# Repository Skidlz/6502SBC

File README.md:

6502SBC
=======

6502 Single Board Computer

Schematics done in eagle 6.1

Source assembles with CA65

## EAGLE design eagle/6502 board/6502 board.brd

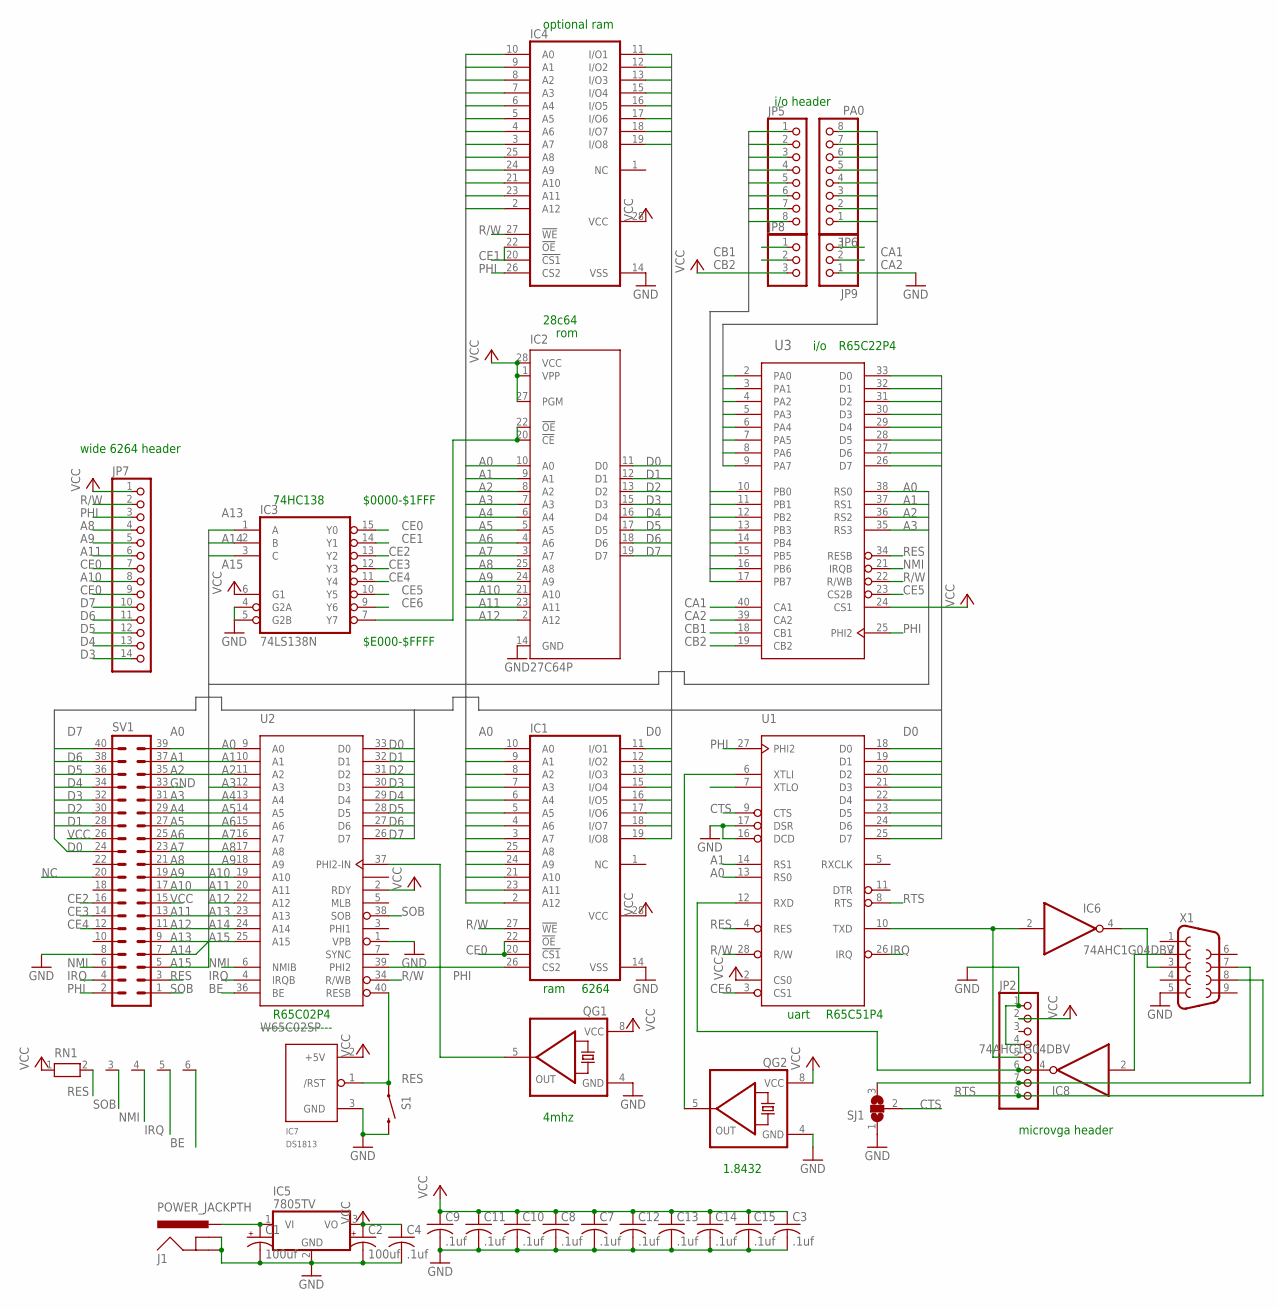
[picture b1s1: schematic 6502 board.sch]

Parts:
C1: 100uf; E3,5-8
C2: 100uf; E2,5-6
C3, C4, C7, C8, C9, C10, C11, C12, C13, C14, C15: .1uf; C025-024X044
IC1, IC4: 6264ASMALL; DIL28-3
IC2: 27C64P; DIL28-6
IC3: 74LS138N; DIL16
IC5: 7805TV; TO220V
IC6, IC8: 74AHC1G04DBV; SOT23-5
IC7: DS1813; TO-92
J1: POWER_JACKPTH; POWER_JACK_PTH
JP2, JP5, JP6: PINHD-1X8BIG; 1X08-BIG
JP7: PINHD-1X14-CB; 1X14-CB
JP8, JP9: PINHD-1X3; 1X03
QG1, QG2: QG5460; DIL08S
RN1: RN05; RN-6
S1: SWITCH-MOMENTARY-2PTH; TACTILE-PTH
SJ1: SJ2WW; SJ_2W
SV1: ML40
U1: G65SC51P; DIP-28
U2: W65C02SP; DIP-40
U3: G65SC22P; DIP-40
X1: DB9FEMALE; DB9

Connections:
A0: IC1.10 (A0), IC2.10 (A0), IC4.10 (A0), SV1.39, U1.13 (RS0), U2.9 (A0), U3.38 (RS0)
A1: IC1.9 (A1), IC2.9 (A1), IC4.9 (A1), SV1.37, U1.14 (RS1), U2.10 (A1), U3.37 (RS1)
A2: IC1.8 (A2), IC2.8 (A2), IC4.8 (A2), SV1.35, U2.11 (A2), U3.36 (RS2)
A3: IC1.7 (A3), IC2.7 (A3), IC4.7 (A3), SV1.31, U2.12 (A3), U3.35 (RS3)
A4: IC1.6 (A4), IC2.6 (A4), IC4.6 (A4), SV1.29, U2.13 (A4)
A5: IC1.5 (A5), IC2.5 (A5), IC4.5 (A5), SV1.27, U2.14 (A5)
A6: IC1.4 (A6), IC2.4 (A6), IC4.4 (A6), SV1.25, U2.15 (A6)
A7: IC1.3 (A7), IC2.3 (A7), IC4.3 (A7), SV1.23, U2.16 (A7)
A8: IC1.25 (A8), IC2.25 (A8), IC4.25 (A8), JP7.4, SV1.21, U2.17 (A8)
A9: IC1.24 (A9), IC2.24 (A9), IC4.24 (A9), JP7.5, SV1.19, U2.18 (A9)
A10: IC1.21 (A10), IC2.21 (A10), IC4.21 (A10), JP7.8, SV1.17, U2.19 (A10)
A11: IC1.23 (A11), IC2.23 (A11), IC4.23 (A11), JP7.6, SV1.13, U2.20 (A11)
A12: IC1.2 (A12), IC2.2 (A12), IC4.2 (A12), SV1.11, U2.22 (A12)
A13: IC3.1 (A), SV1.9, U2.23 (A13)
A14: IC3.2 (B), SV1.7, U2.24 (A14)
A15: IC3.3 (C), SV1.5, U2.25 (A15)
BE: RN1.6, U2.36 (BE)
CA1: JP9.3, U3.40 (CA1)
CA2: JP9.2, U3.39 (CA2)
CB1: JP8.1, U3.18 (CB1)
CB2: JP8.2, U3.19 (CB2)
CE0: IC1.20 (!CS1), IC1.22 (!OE), IC3.15 (Y0), JP7.7, JP7.9
CE1: IC3.14 (Y1), IC4.20 (!CS1), IC4.22 (!OE)
CE2: IC3.13 (Y2), SV1.16
CE3: IC3.12 (Y3), SV1.14
CE4: IC3.11 (Y4), SV1.12
CE5: IC3.10 (Y5), U3.23 (CS2B)
CE6: IC3.9 (Y6), U1.3 (CS1)
CTS: SJ1.2, U1.9 (CTS)
D0: IC1.11 (I/O1), IC2.11 (D0), IC4.11 (I/O1), SV1.24, U1.18 (D0), U2.33 (D0), U3.33 (D0)
D1: IC1.12 (I/O2), IC2.12 (D1), IC4.12 (I/O2), SV1.28, U1.19 (D1), U2.32 (D1), U3.32 (D1)
D2: IC1.13 (I/O3), IC2.13 (D2), IC4.13 (I/O3), SV1.30, U1.20 (D2), U2.31 (D2), U3.31 (D2)
D3: IC1.15 (I/O4), IC2.15 (D3), IC4.15 (I/O4), JP7.14, SV1.32, U1.21 (D3), U2.30 (D3), U3.30 (D3)
D4: IC1.16 (I/O5), IC2.16 (D4), IC4.16 (I/O5), JP7.13, SV1.34, U1.22 (D4), U2.29 (D4), U3.29 (D4)
D5: IC1.17 (I/O6), IC2.17 (D5), IC4.17 (I/O6), JP7.12, SV1.36, U1.23 (D5), U2.28 (D5), U3.28 (D5)
D6: IC1.18 (I/O7), IC2.18 (D6), IC4.18 (I/O7), JP7.11, SV1.38, U1.24 (D6), U2.27 (D6), U3.27 (D6)
D7: IC1.19 (I/O8), IC2.19 (D7), IC4.19 (I/O8), JP7.10, SV1.40, U1.25 (D7), U2.26 (D7), U3.26 (D7)
GND: C1.-, C2.-, C3.2, C4.2, C7.2, C8.2, C9.2, C10.2, C11.2, C12.2, C13.2, C14.2, C15.2, IC1.14 (VSS), IC2.14 (GND), IC3.4 (G2A), IC3.5 (G2B), IC3.8 (GND), IC4.14 (VSS), IC5.2 (GND), IC6.3 (GND), IC7.3 (GND), IC8.3 (GND), J1.GND, J1.GNDBREAK, JP2.1, JP2.4, JP9.1, QG1.4 (GND), QG2.4 (GND), S1.3 (2), SJ1.1, SV1.8, SV1.33, U1.16 (DCD), U1.17 (DSR), U2.1 (VPB), X1.5
IRQ: RN1.5, SV1.4, U1.26 (IRQ), U2.4 (IRQB)
unnamed: QG1.5 (OUT), U2.37 (PHI2-IN)
unnamed: IC2.20 (!CE), IC2.22 (!OE), IC3.7 (Y7)
unnamed: IC6.4 (O), X1.3
unnamed: IC8.2 (I), X1.2
unnamed: JP2.7, SJ1.3, X1.7
unnamed: QG2.5 (OUT), U1.6 (XTLI)
unnamed: IC6.2 (I), JP2.5, U1.10 (TXD)
unnamed: IC8.4 (O), JP2.6, U1.12 (RXD)
unnamed: C1.+, IC5.1 (VI), J1.PWR
NC: SV1.20
NMI: RN1.4, SV1.6, U2.6 (NMIB), U3.21 (IRQB)
PA0: JP6.8, U3.2 (PA0)
PA1: JP6.7, U3.3 (PA1)
PA2: JP6.6, U3.4 (PA2)
PA3: JP6.5, U3.5 (PA3)
PA4: JP6.4, U3.6 (PA4)
PA5: JP6.3, U3.7 (PA5)
PA6: JP6.2, U3.8 (PA6)
PA7: JP6.1, U3.9 (PA7)
PB0: JP5.1, U3.10 (PB0)
PB1: JP5.2, U3.11 (PB1)
PB2: JP5.3, U3.12 (PB2)
PB3: JP5.4, U3.13 (PB3)
PB4: JP5.5, U3.14 (PB4)
PB5: JP5.6, U3.15 (PB5)
PB6: JP5.7, U3.16 (PB6)
PB7: JP5.8, U3.17 (PB7)
PHI: IC1.26 (CS2), IC4.26 (CS2), JP7.3, SV1.2, U1.27 (PHI2), U2.39 (PHI2), U3.25 (PHI2)
R/W: IC1.27 (!WE), IC4.27 (!WE), JP7.2, U1.28 (R/W), U2.34 (R/WB), U3.22 (R/WB)
RES: IC7.1 (/RST), RN1.2, S1.1, SV1.3, U1.4 (RES), U2.40 (RESB), U3.34 (RESB)
RTS: JP2.8, U1.8 (RTS), X1.8
SOB: RN1.3, SV1.1, U2.38 (SOB)
VCC: C2.+, C3.1, C4.1, C7.1, C8.1, C9.1, C10.1, C11.1, C12.1, C13.1, C14.1, C15.1, IC1.28 (VCC), IC2.1 (VPP), IC2.27 (PGM), IC2.28 (VCC), IC3.6 (G1), IC3.16 (VCC), IC4.28 (VCC), IC5.3 (VO), IC6.5 (VCC), IC7.2 (+5V), IC8.5 (VCC), JP2.2, JP7.1, JP8.3, QG1.8 (VCC), QG2.8 (VCC), RN1.1, SV1.15, SV1.26, U1.2 (CS0), U2.2 (RDY), U3.24 (CS1)
VDD: U1.15 (VDD), U2.8 (VDD), U3.20 (VDD)
VSS: U1.1 (VSS), U2.21 (VSS), U3.1 (VSS)

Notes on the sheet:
microvga header
rom
ram
4mhz
1.8432
$0000-$1FFF
$E000-$FFFF
uart
i/o
R65C22P4
R65C51P4
R65C02P4
------------------
6264
i/o header
28c64
74HC138
optional ram
wide 6264 header

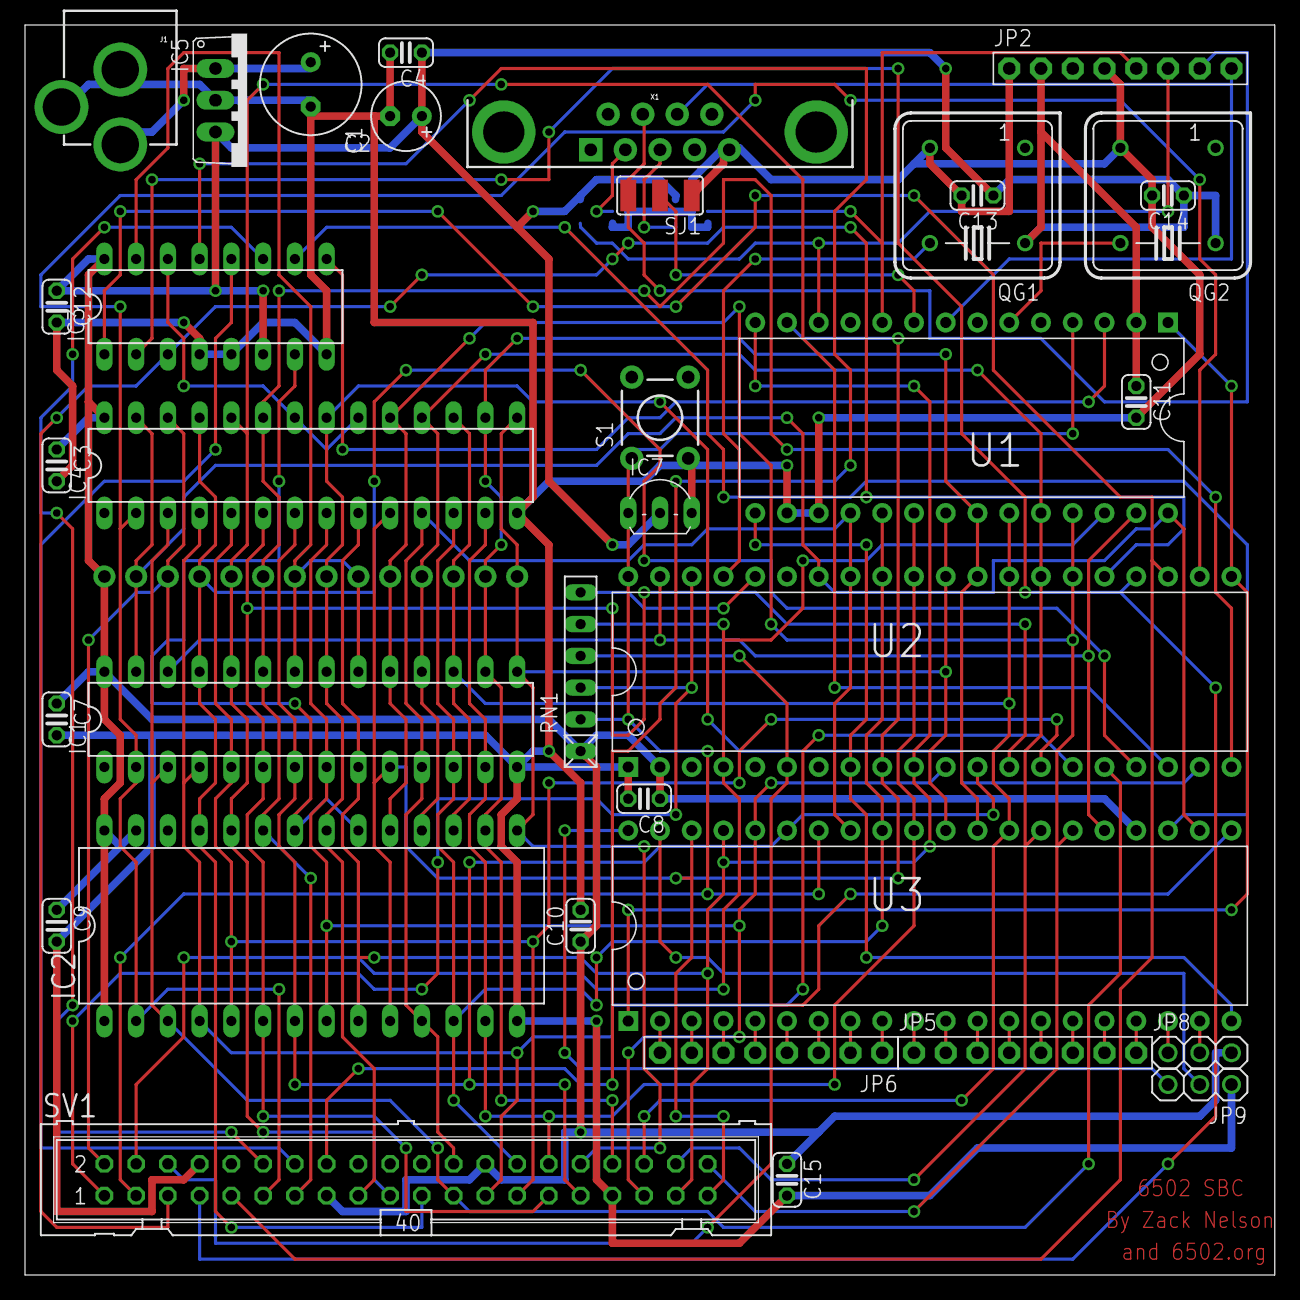
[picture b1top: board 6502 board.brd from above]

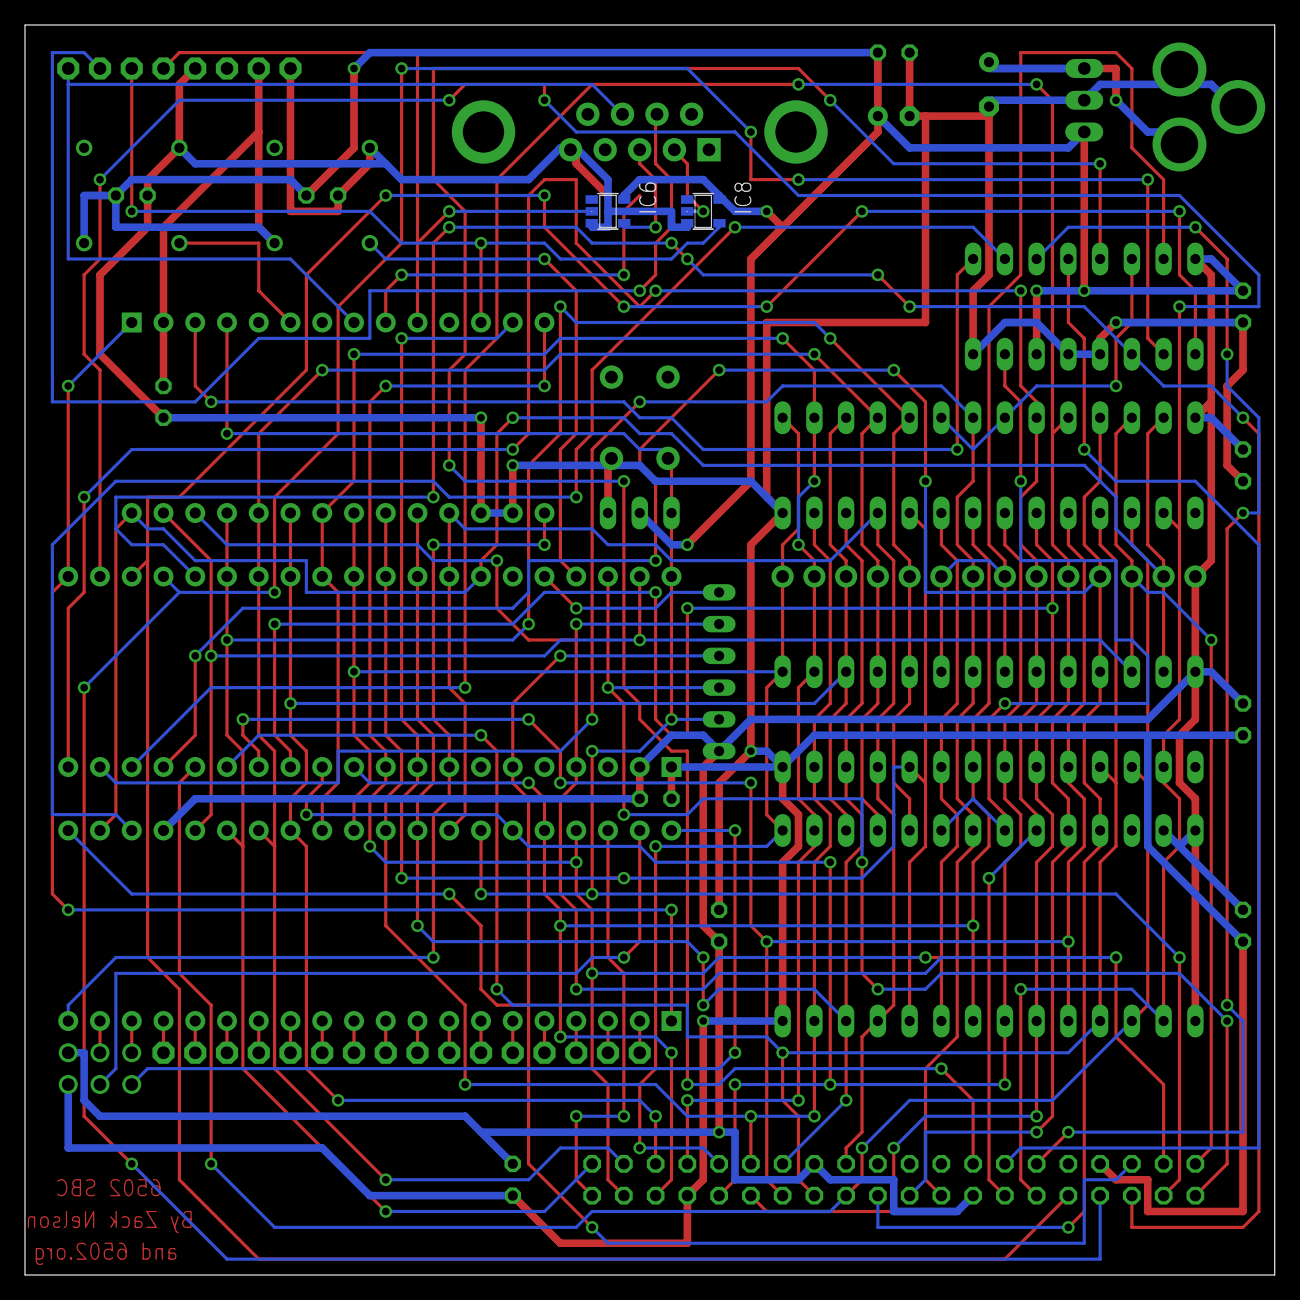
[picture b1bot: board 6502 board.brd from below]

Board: 2 copper layers, 100.0 x 100.0 mm, 38 parts (2 on the bottom side), 73 nets.

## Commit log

2014-01-04 Schematic and Source
2014-01-04 Readme

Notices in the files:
parts and their libraries:
SparkFun: Licensing: CC v3.0 Share-Alike You are welcome to use this library for commercial purposes.
